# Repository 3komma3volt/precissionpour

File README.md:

# Precision Pour

A game for people who have trouble to stay hydrated. Grab a glass of water or some juice and get your liquid in a playful way.  
The first version used a regular kitchen scale with made-up rules. This motivated creating this portable, ready-to-play game.

It consists of load cells available in several weight grades, a 3D-printed enclosure and a custom PCB with touchscreen and LiPo charger.

## Features

- **Weight Capacity**: Depending on used load cell (recommended 2kg)
- **Accuracy**: About 0.2g
- **Display**: 320x240 TFT with touch screen
- **Battery Life**: ~4 hours of gameplay (with 1000mAh LiPo)
- **Charging**: USB-C
- **Multiplayer**: Up to 10 players
- **Game Modes**: Target & Darts

## Gameplay

Be sure the battery is charged (using the USB-C connector).
First press anywhere on the splash screen to enter the game mode selection screen. There you can set the number of players.

### Target

In the target mode, you set the number of rounds to play and an amount of liquid to drink in ml (it's assumed that 1ml is 1g).
After this the first player has to place the drink on the platform and press "Weight". This measures the tare weight. So it is possible to change the drink during the game.
Then the player has to drink the amount that the screen says in the section "Target", place it on the platform again and press "Drink and weight".
After this, the difference of the first and second measurement is used and subtracted from the target value. Everything below 1g of tolerance is added as malus points.
Then it is the next player's turn. After the selected number of rounds, a screen shows the malus points of all players sorted from winner to loser.

### Darts

This is a game mode where the players have to drink down from 301ml.
The gameplay is the same as in target mode, with the difference that the maximum value is 60ml (as triple 20 in darts). If the value is below 60 or higher as the remaining score of the player, it is a failure "throw" and does not count.
The first who manages to reduce his score to zero wins.

## Hardware

### Electronics

The PCB is designed so it can be ordered directly from JLCPCB. It is based on a 2432S028 ESP32 development board with TFT which was used before creating the custom PCB adding the battery charger and load cell amplifier.

You will also need:
- A load cell with a 1 or 2kg range: https://de.aliexpress.com/item/1005006892146384.html
- A TFT display with touch: https://de.aliexpress.com/item/1005008045337422.html
- A LiPo battery. The game draws about 220mA, so a 1000mAh battery would last about 4h of gameplay.
- Some JST XH connectors (1x2 and 1x4) to connect the battery and the load cell
- A 6x6mm push button

Crimp the battery connector contacts and pin them as the silk screen shows.
Crimp the load cell as the silk screen shows.
Solder the push button on the back side of the PCB.
Solder the display to the back side of the PCB. This is a bit tricky since the flat ribbon connector takes some experience to solder. After that, use some double sided tape to fix the display to the PCB.

### Housing & CAD

Print the STL files from the housing folder. Depending on your printer, maybe the upper shell needs some support on the display hole. 

Print 
1x lower_shell.stl
1x upper_shell_mainboard.stl
1x scaleplate.stl
1x top_protection_ring.stl (optional)

### Assembly

For assembly you will need:
- 2x M4x20 countersunk screws
- 2x M5x20 screws
- 6x M3x12 countersunk screws
- 4x M3x8 screws
- Some zip ties

The types of the screws do not really matter, use what you have in stock.

Screw the load cell to the lower shell using the M5 screws. You can use the little pods on the base plate to strap the cables down with zip ties.
Strap down the battery using the pods with zip ties. 
Insert the PCB and use the M3 screws to mount it.
Connect the battery and the load cell with the PCB and close the housing. Use the countersunk M3 screws to close the housing.
Now you can use glue to glue the protection ring around the big top opening. This shall prevent fluid to flow into the device.
Put the scaleplate.stl on top and use the M4 countersunk screw to mount it. 

## Development

### Tools & Technologies

- **3D Design**: [Solvespace](https://solvespace.com/)
- **Electronics**: [KiCad](https://www.kicad.org/)
- **Firmware**: [PlatformIO](https://platformio.org/)
- **UI**: [SquareLine Studio](https://squareline.io)

### Build & Upload

Connect the device with a PC using the USB-C connector. Turn it on by long-pressing (>1s) the button. After this, a new COM port should be detected. 
Build and upload and the display should turn on.

Use PlatformIO CLI in the `Firmware/` folder:

```bash
# Build
pio run
# Upload (auto-detects COM port)
pio run -t upload
# Optional: specify environment and COM port
pio run -e <env> -t upload --upload-port COM5
```

### Calibration

For the first time, a setup has to be done by pressing the gear-button on the splash screen.
There remove everything from the upper plate and press the tare button. Then add a known weight and set its weight in grams using the buttons on the screen, then press set. After this, the game is calibrated.

### Project Structure

```
Firmware/       - ESP32 firmware source code
Housing/        - 3D models and CAD files
Schematic/      - PCB design and schematics
assets/         - Images and media files
```

---

## To-Do

- [ ] Fixing the audio output

---

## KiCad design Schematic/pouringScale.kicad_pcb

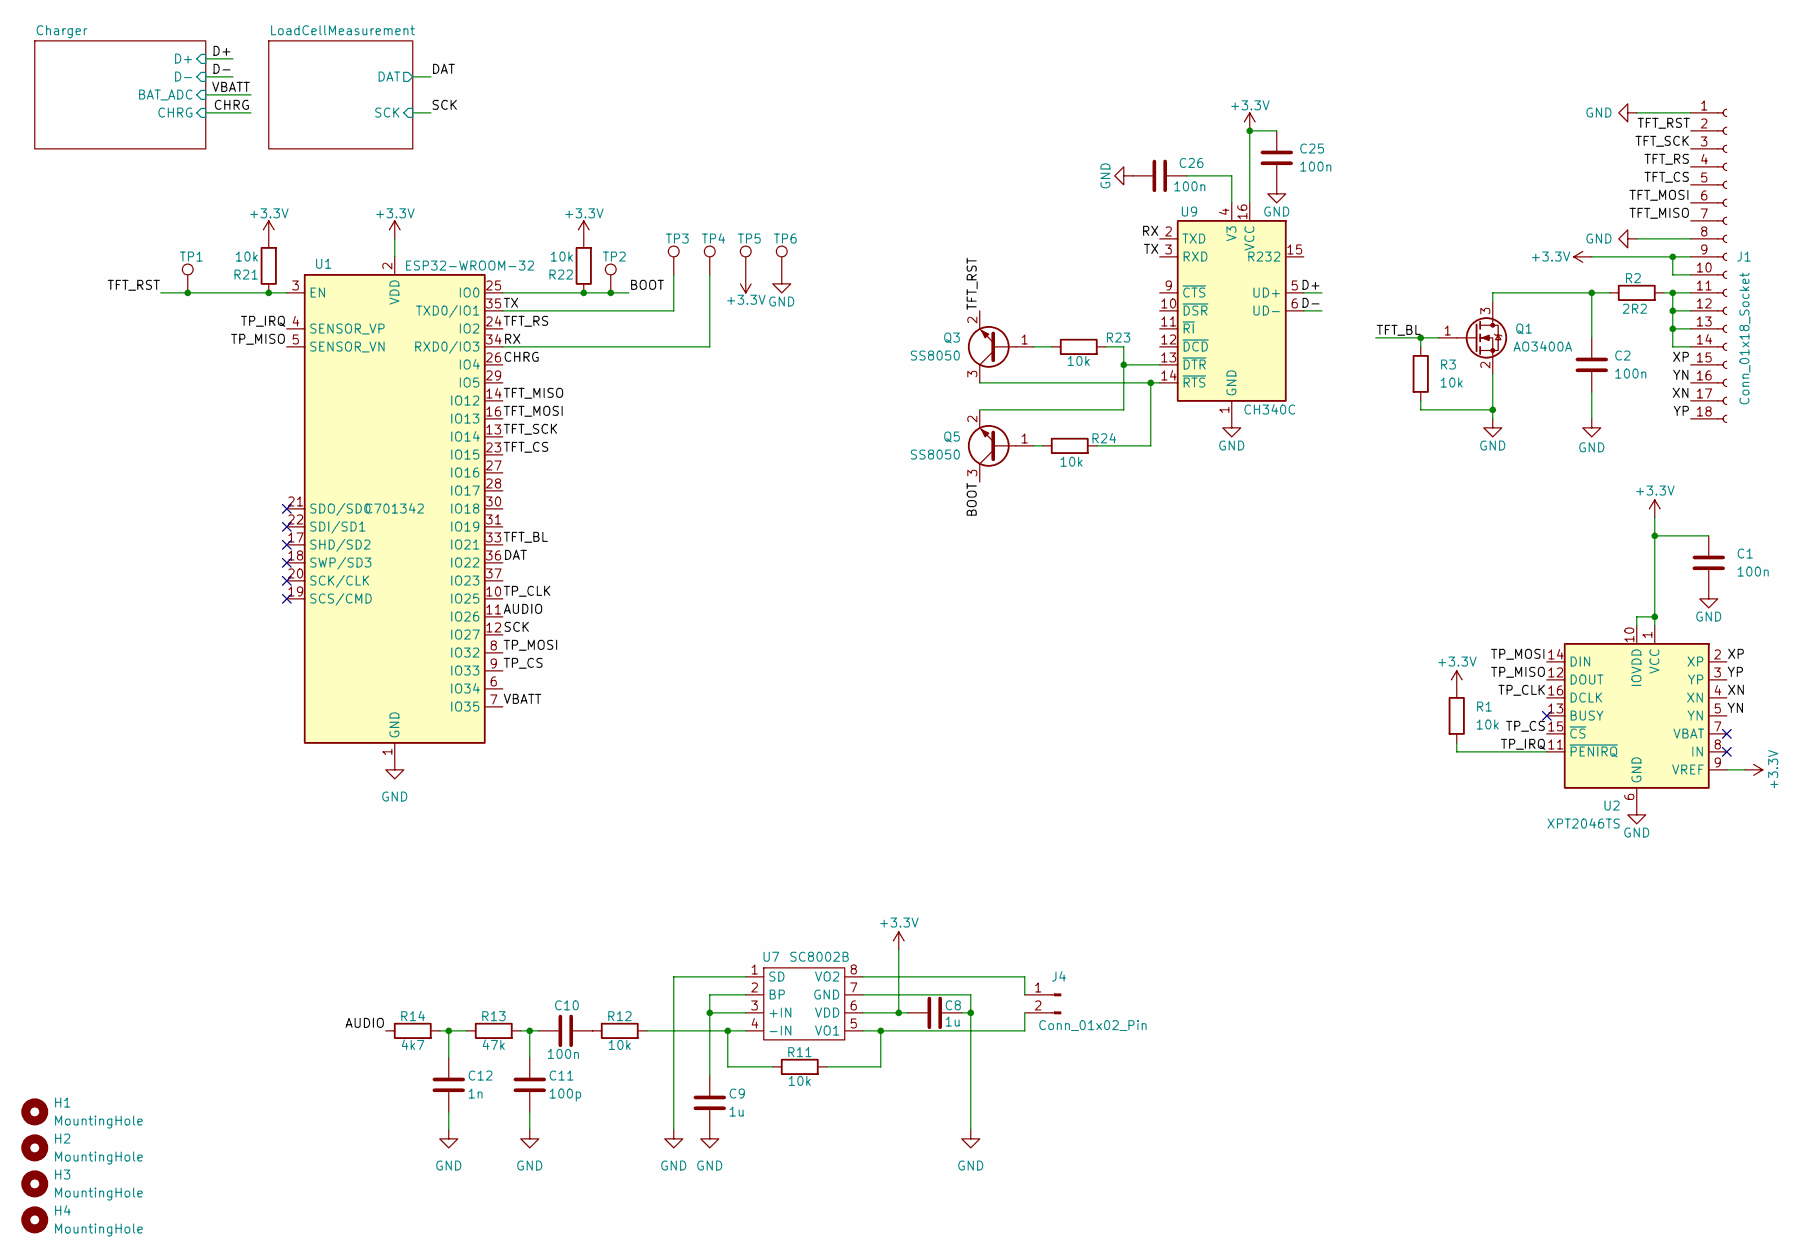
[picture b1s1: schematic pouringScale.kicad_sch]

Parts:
C1, C2, C10, C25, C26: 100n; C_0603_1608Metric; LCSC C14663
C8, C9: 1u; C_0603_1608Metric; LCSC C15849
C11: 100p; C_0603_1608Metric; LCSC C14858
C12: 1n; C_0603_1608Metric; LCSC C1588
H1, H2, H3, H4: MountingHole; MountingHole_3.2mm_M3_ISO7380
J1: Conn_01x18_Socket; display
J4: Conn_01x02_Pin; JST_XH_B2B-XH-AM_1x02_P2.50mm_Vertical
Q1: AO3400A; SOT-23; LCSC C20917
Q3, Q5: SS8050; SOT-23; LCSC C2150
R1, R3, R11, R12, R21, R22, R23, R24: 10k; R_0603_1608Metric; LCSC C25804
R2: 2R2; R_0603_1608Metric; LCSC C22939
R13: 47k; R_0603_1608Metric; LCSC C25819
R14: 4k7; R_0603_1608Metric; LCSC C23162
TP1: EN; TestPoint_Pad_D1.5mm
TP2: Boot; TestPoint_Pad_D1.5mm
TP3: Tx; TestPoint_Pad_D1.5mm
TP4: Rx; TestPoint_Pad_D1.5mm
TP5: 3V3; TestPoint_Pad_D1.5mm
TP6: GND; TestPoint_Pad_D1.5mm
U1: ESP32-WROOM-32; ESP32-WROOM-32U; LCSC C701342
U2: XPT2046TS; TSSOP-16_4.4x5mm_P0.65mm; LCSC C19076
U7: SC8002B; SOP-8_3.9x4.9mm_P1.27mm; LCSC C82124
U9: CH340C; SOIC-16_3.9x9.9mm_P1.27mm; LCSC C84681

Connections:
+3.3V: C1.1, C8.2, C25.1, J1.9, J1.10, R1.1, R21.2, R22.2, TP5.1, U1.2 (VDD), U2.1 (VCC), U2.9 (VREF), U2.10 (IOVDD), U7.6 (VDD), U9.16 (VCC); also elsewhere on the board
/AUDIO: R14.1, U1.11 (IO26)
/BOOT: Q5.3 (C), R22.1, TP2.1, U1.25 (IO0)
/CHRG: U1.26 (IO4); also elsewhere on the board
/D+: U9.5 (UD+); also elsewhere on the board
/D-: U9.6 (UD-); also elsewhere on the board
/DAT: U1.36 (IO22); also elsewhere on the board
/RX: TP4.1, U1.34 (RXD0/IO3), U9.2 (TXD)
/SCK: U1.12 (IO27); also elsewhere on the board
/TFT_BL: Q1.1 (G), R3.1, U1.33 (IO21)
/TFT_CS: J1.5, U1.23 (IO15)
/TFT_MISO: J1.7, U1.14 (IO12)
/TFT_MOSI: J1.6, U1.16 (IO13)
/TFT_RS: J1.4, U1.24 (IO2)
/TFT_RST: J1.2, Q3.2 (E), R21.1, TP1.1, U1.3 (EN)
/TFT_SCK: J1.3, U1.13 (IO14)
/TP_CLK: U1.10 (IO25), U2.16 (DCLK)
/TP_CS: U1.9 (IO33), U2.15 (~CS)
/TP_IRQ: R1.2, U1.4 (SENSOR_VP), U2.11 (~PENIRQ)
/TP_MISO: U1.5 (SENSOR_VN), U2.12 (DOUT)
/TP_MOSI: U1.8 (IO32), U2.14 (DIN)
/TX: TP3.1, U1.35 (TXD0/IO1), U9.3 (RXD)
/VBATT: U1.7 (IO35); also elsewhere on the board
/XN: J1.17, U2.4 (XN)
/XP: J1.15, U2.2 (XP)
/YN: J1.16, U2.5 (YN)
/YP: J1.18, U2.3 (YP)
GND: C1.2, C2.2, C8.1, C9.2, C11.2, C12.2, C25.2, C26.2, J1.1, J1.8, Q1.2 (S), R3.2, TP6.1, U1.1 (GND), U1.15 (GND), U1.38 (GND), U1.39 (GND), U2.6 (GND), U7.1 (SD), U7.7 (GND), U9.1 (GND); also elsewhere on the board
unnamed: C10.1, R12.1
unnamed: C10.2, C11.1, R13.2
unnamed: C12.1, R13.1, R14.2
unnamed: J1.11, J1.12, J1.13, J1.14, R2.2
unnamed: J4.1, U7.8 (VO2)
unnamed: J4.2, R11.2, U7.5 (VO1)
unnamed: C2.1, Q1.3 (D), R2.1
unnamed: Q3.1 (B), R23.1
unnamed: Q3.3 (C), R24.2, U9.14 (~RTS)
unnamed: Q5.1 (B), R24.1
unnamed: Q5.2 (E), R23.2, U9.13 (~DTR)
unnamed: C9.1, U7.2 (BP), U7.3 (+IN)
unnamed: R11.1, R12.2, U7.4 (-IN)
unnamed: C26.1, U9.4 (V3)

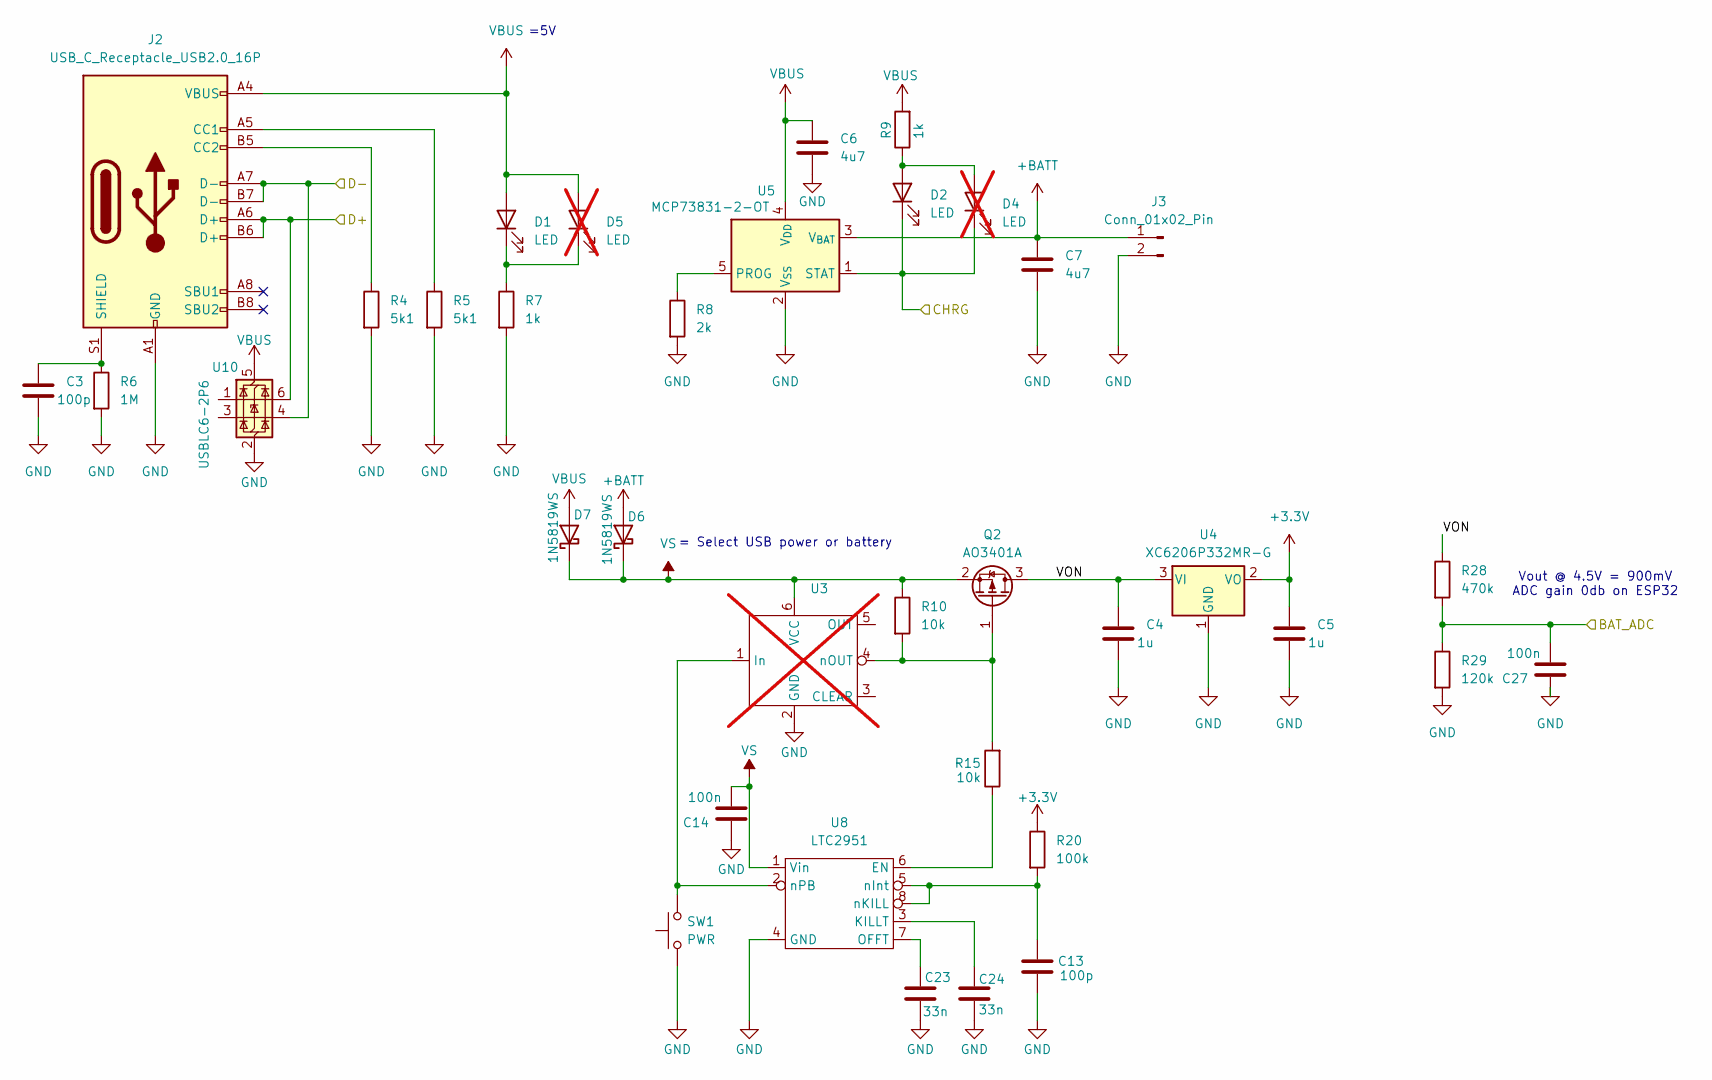
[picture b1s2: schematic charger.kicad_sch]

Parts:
C3, C13: 100p; C_0603_1608Metric; LCSC C14858
C4, C5: 1u; C_0603_1608Metric; LCSC C15849
C6, C7: 4u7; C_0603_1608Metric; LCSC C19666
C14, C27: 100n; C_0603_1608Metric; LCSC C14663
C23, C24: 33n; C_0603_1608Metric; LCSC C21117
D1, D2: LED; LED_0603_1608Metric; LCSC C2286
D4, D5: LED; LED_0603_1608Metric; LCSC C2286; not fitted
D6, D7: 1N5819WS; D_SOD-323; LCSC C191023
J2: USB_C_Receptacle_USB2.0_16P; USB_C_Receptacle_HRO_TYPE-C-31-M-12; LCSC C165948
J3: Conn_01x02_Pin; JST_XH_B2B-XH-AM_1x02_P2.50mm_Vertical
Q2: AO3401A; SOT-23; LCSC C15127
R4, R5: 5k1; R_0603_1608Metric; LCSC C23186
R6: 1M; R_0603_1608Metric; LCSC C22935
R7, R9: 1k; R_0603_1608Metric; LCSC C21190
R8: 2k; R_0603_1608Metric; LCSC C22975
R10, R15: 10k; R_0603_1608Metric; LCSC C25804
R20: 100k; C_0603_1608Metric; LCSC C25803
R28: 470k; R_0603_1608Metric; LCSC C23178
R29: 120k; R_0603_1608Metric; LCSC C25576
SW1: PWR; SW_PUSH_6mm
U3: SOT-23-6; LCSC C79401; not fitted
U4: XC6206P332MR-G; SOT-23-3; LCSC C5446
U5: MCP73831-2-OT; SOT-23-5; LCSC C424093
U8: LTC2951; TSOT-23-8; LCSC C683762
U10: USBLC6-2P6; SOT-666; LCSC C15999

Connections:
+3.3V: C5.1, R20.1, U4.2 (VO); also elsewhere on the board
+BATT: C7.1, D6.2 (A), J3.1, U5.3 (V_{BAT})
/CHRG: D2.1 (K), D4.1 (K), U5.1 (STAT); also elsewhere on the board
/Charger/VON: C4.1, Q2.3 (D), R28.1, U4.3 (VI)
/D+: J2.A6 (D+), J2.B6 (D+), U10.6 (I/O1); also elsewhere on the board
/D-: J2.A7 (D-), J2.B7 (D-), U10.4 (I/O2); also elsewhere on the board
/VBATT: C27.2, R28.2, R29.1; also elsewhere on the board
GND: C3.2, C4.2, C5.2, C6.2, C7.2, C13.2, C14.1, C23.2, C24.2, C27.1, J2.A1 (GND), J2.A12 (GND), J2.B1 (GND), J2.B12 (GND), J3.2, R4.2, R5.2, R6.2, R7.2, R8.2, R29.2, SW1.1, U3.2 (GND), U4.1 (GND), U5.2 (V_{SS}), U8.4 (GND), U10.2 (GND); also elsewhere on the board
unnamed: D1.1 (K), D5.1 (K), R7.1
unnamed: D2.2 (A), D4.2 (A), R9.1
unnamed: J2.A5 (CC1), R5.1
unnamed: J2.B5 (CC2), R4.1
unnamed: C3.1, J2.S1 (SHIELD), R6.1
unnamed: Q2.1 (G), R10.2, R15.2, U3.4 (nOUT)
unnamed: SW1.2, U3.1 (In), U8.2 (nPB)
unnamed: R8.1, U5.5 (PROG)
unnamed: R15.1, U8.6 (EN)
unnamed: C24.1, U8.3 (KILLT)
unnamed: C23.1, U8.7 (OFFT)
unnamed: C13.1, R20.2, U8.5 (nInt), U8.8 (nKILL)
VBUS: C6.1, D1.2 (A), D5.2 (A), D7.2 (A), J2.A4 (VBUS), J2.A9 (VBUS), J2.B4 (VBUS), J2.B9 (VBUS), R9.2, U5.4 (V_{DD}), U10.5 (VBUS)
VS: C14.2, D6.1 (K), D7.1 (K), Q2.2 (S), R10.1, U3.6 (VCC), U8.1 (Vin)

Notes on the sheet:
= Select USB power or battery
=5V
Vout @ 4.5V = 900mV ADC gain 0db on ESP32

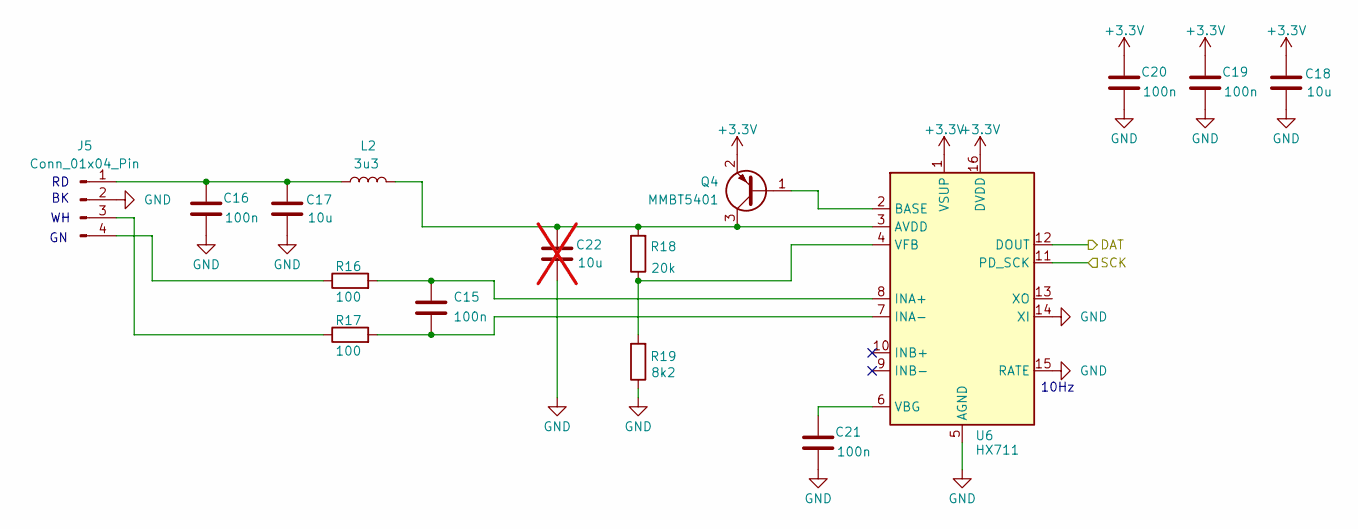
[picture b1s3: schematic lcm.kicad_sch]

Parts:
C15, C16, C19, C20, C21: 100n; C_0603_1608Metric; LCSC C14663
C17, C18: 10u; C_1206_3216Metric; LCSC C13585
C22: 10u; C_1206_3216Metric; LCSC C13585; not fitted
J5: Conn_01x04_Pin; JST_XH_B4B-XH-A_1x04_P2.50mm_Vertical
L2: 3u3; L_0805_2012Metric; LCSC C1017
Q4: MMBT5401; SOT-23; LCSC C8326
R16, R17: 100; C_0603_1608Metric; LCSC C22775
R18: 20k; C_0603_1608Metric; LCSC C4184
R19: 8k2; C_0603_1608Metric; LCSC C25981
U6: HX711; SOP-16_3.9x9.9mm_P1.27mm; LCSC C6705483

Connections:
+3.3V: C18.1, C19.1, C20.1, Q4.2 (E), U6.1 (VSUP), U6.16 (DVDD); also elsewhere on the board
/DAT: U6.12 (DOUT); also elsewhere on the board
/SCK: U6.11 (PD_SCK); also elsewhere on the board
GND: C16.2, C17.2, C18.2, C19.2, C20.2, C21.2, C22.2, J5.2, R19.1, U6.5 (AGND), U6.14 (XI), U6.15 (RATE); also elsewhere on the board
unnamed: C16.1, C17.1, J5.1, L2.1
unnamed: J5.3, R17.1
unnamed: J5.4, R16.1
unnamed: Q4.1 (B), U6.2 (BASE)
unnamed: C22.1, L2.2, Q4.3 (C), R18.2, U6.3 (AVDD)
unnamed: C15.1, R16.2, U6.8 (INA+)
unnamed: C15.2, R17.2, U6.7 (INA-)
unnamed: C21.1, U6.6 (VBG)
unnamed: R18.1, R19.2, U6.4 (VFB)

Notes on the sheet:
10Hz

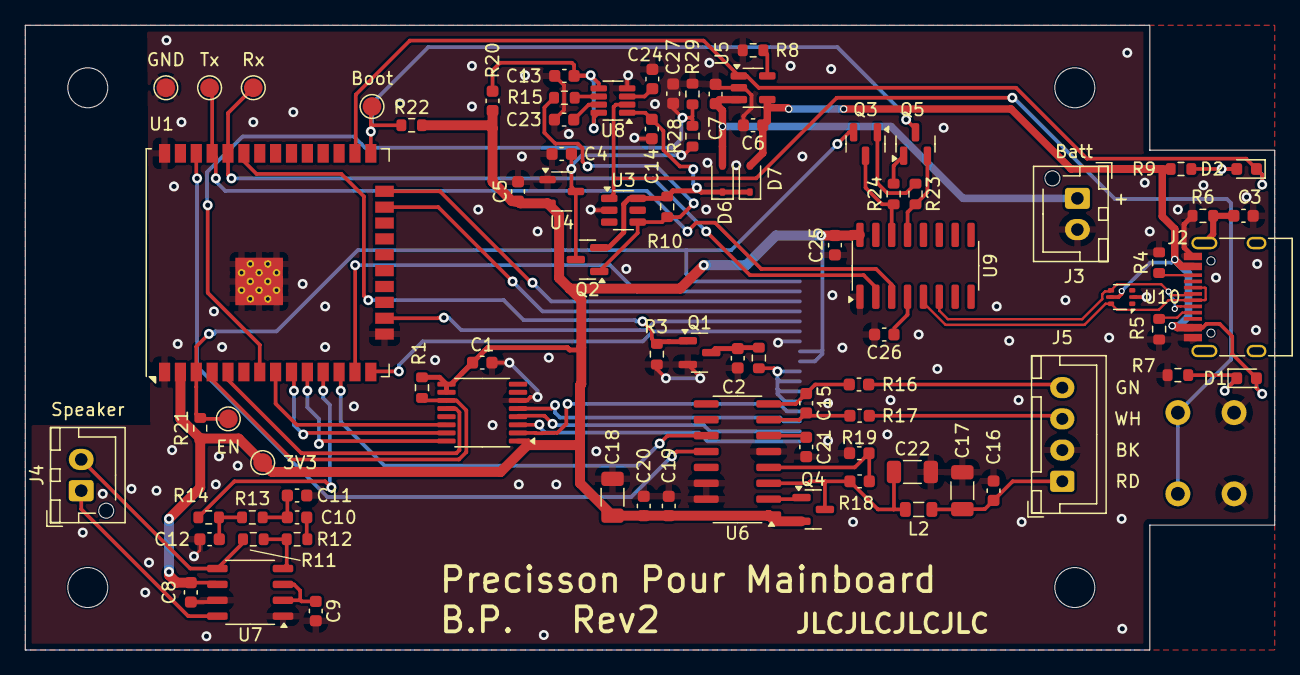
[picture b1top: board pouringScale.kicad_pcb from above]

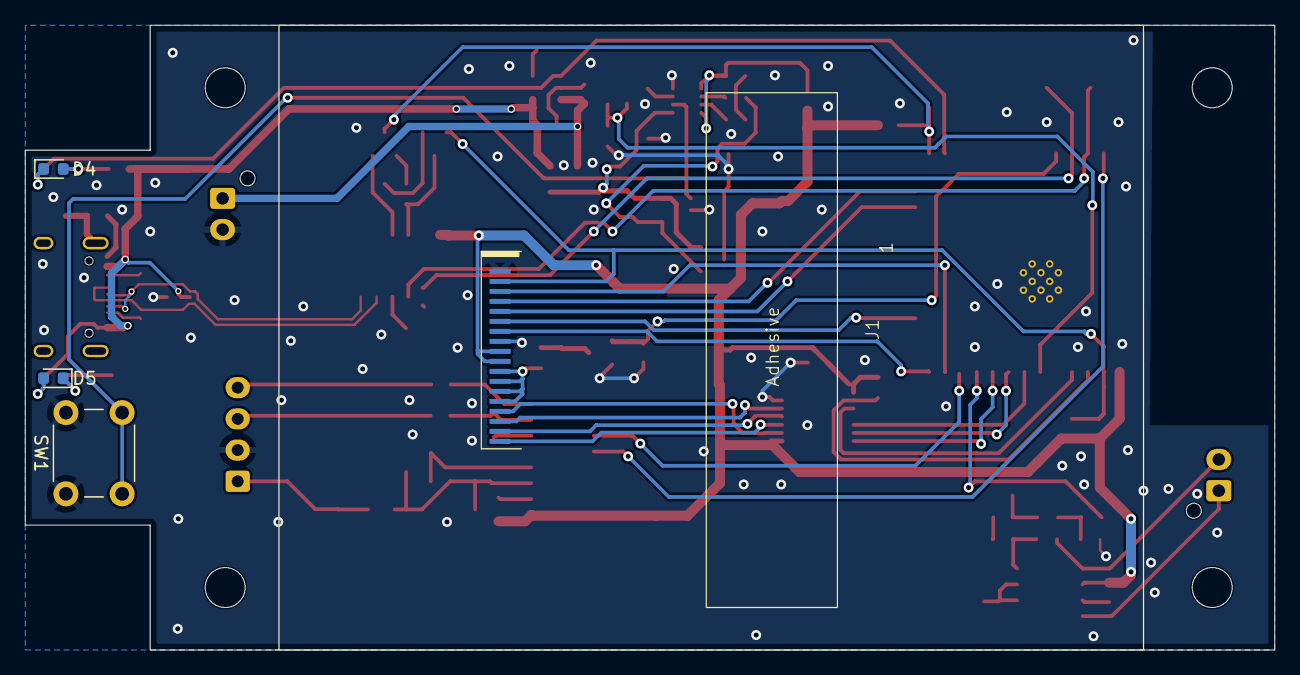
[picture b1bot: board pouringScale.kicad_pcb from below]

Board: 2 copper layers, 100.0 x 50.0 mm, 91 parts (3 on the bottom side), 67 nets.
